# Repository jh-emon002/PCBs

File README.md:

## Images of the PCBs

### 1. AC to DC converter
A simple full bridge diode rectifier with smoothing capacitor and an indicator LED. It takes AC input in one side and outputs DC in the another.

### 2. Transformerless Power Supply
A 70x40 mm PCB that takes 110-220V AC at one side and outputs a stable 5V DC at another terminal. As there is no transformer, the circuit is compact and cheap.

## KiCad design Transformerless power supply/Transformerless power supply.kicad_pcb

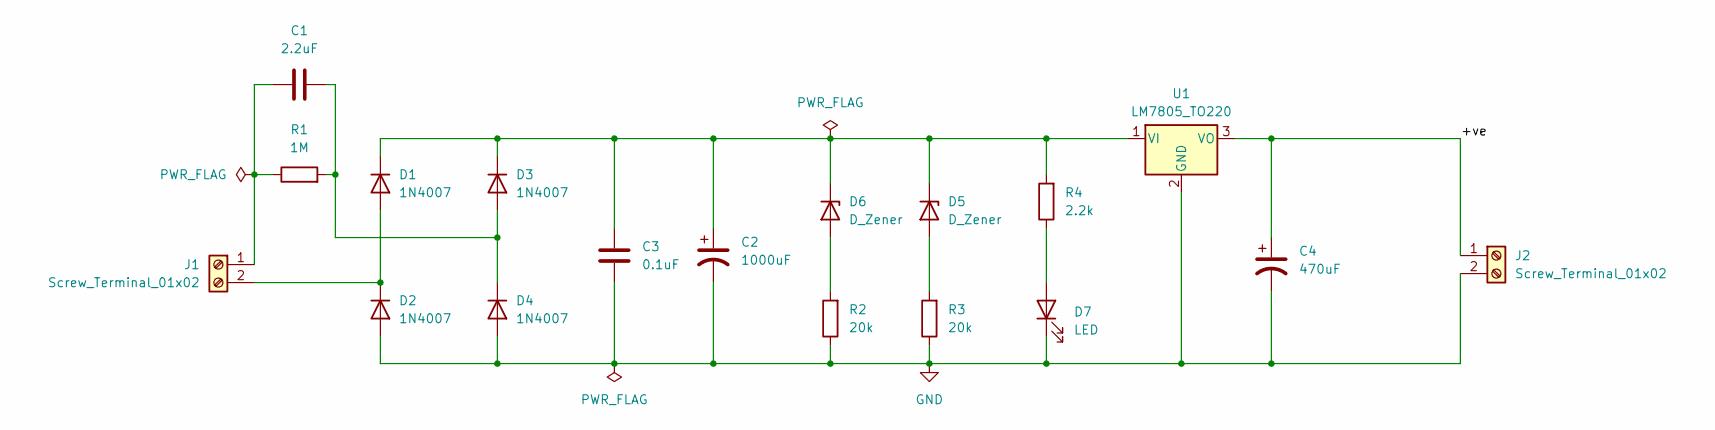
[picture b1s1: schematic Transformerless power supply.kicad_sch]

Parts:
C1: 2.2uF; C_Rect_L18.0mm_W5.0mm_P15.00mm_FKS3_FKP3
C2: 1000uF; CP_Radial_D10.0mm_P2.50mm
C3: 0.1uF; C_Disc_D4.7mm_W2.5mm_P5.00mm
C4: 470uF; CP_Radial_D10.0mm_P2.50mm
D1, D2, D3, D4: 1N4007; D_DO-41_SOD81_P10.16mm_Horizontal
D5, D6: D_Zener; D_DO-201_P15.24mm_Horizontal
D7: LED; LED_D5.0mm
J1, J2: Screw_Terminal_01x02; TerminalBlock_MaiXu_MX126-5.0-02P_1x02_P5.00mm
R1: 1M; R_Axial_DIN0204_L3.6mm_D1.6mm_P5.08mm_Horizontal
R2, R3: 20k; R_Axial_DIN0204_L3.6mm_D1.6mm_P5.08mm_Horizontal
R4: 2.2k; R_Axial_DIN0204_L3.6mm_D1.6mm_P5.08mm_Horizontal
U1: LM7805_TO220; TO-220-3_Vertical

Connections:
/+ve: C4.1, J2.1, U1.3 (VO)
GND: C2.2, C3.2, C4.2, D2.2 (A), D4.2 (A), D7.1 (K), J2.2, R2.1, R3.1, U1.2 (GND)
unnamed: D1.2 (A), D2.1 (K), J1.2
unnamed: C2.1, C3.1, D1.1 (K), D3.1 (K), D5.1 (K), D6.1 (K), R4.2, U1.1 (VI)
unnamed: C1.2, D3.2 (A), D4.1 (K), R1.2
unnamed: D5.2 (A), R3.2
unnamed: D6.2 (A), R2.2
unnamed: D7.2 (A), R4.1
unnamed: C1.1, J1.1, R1.1

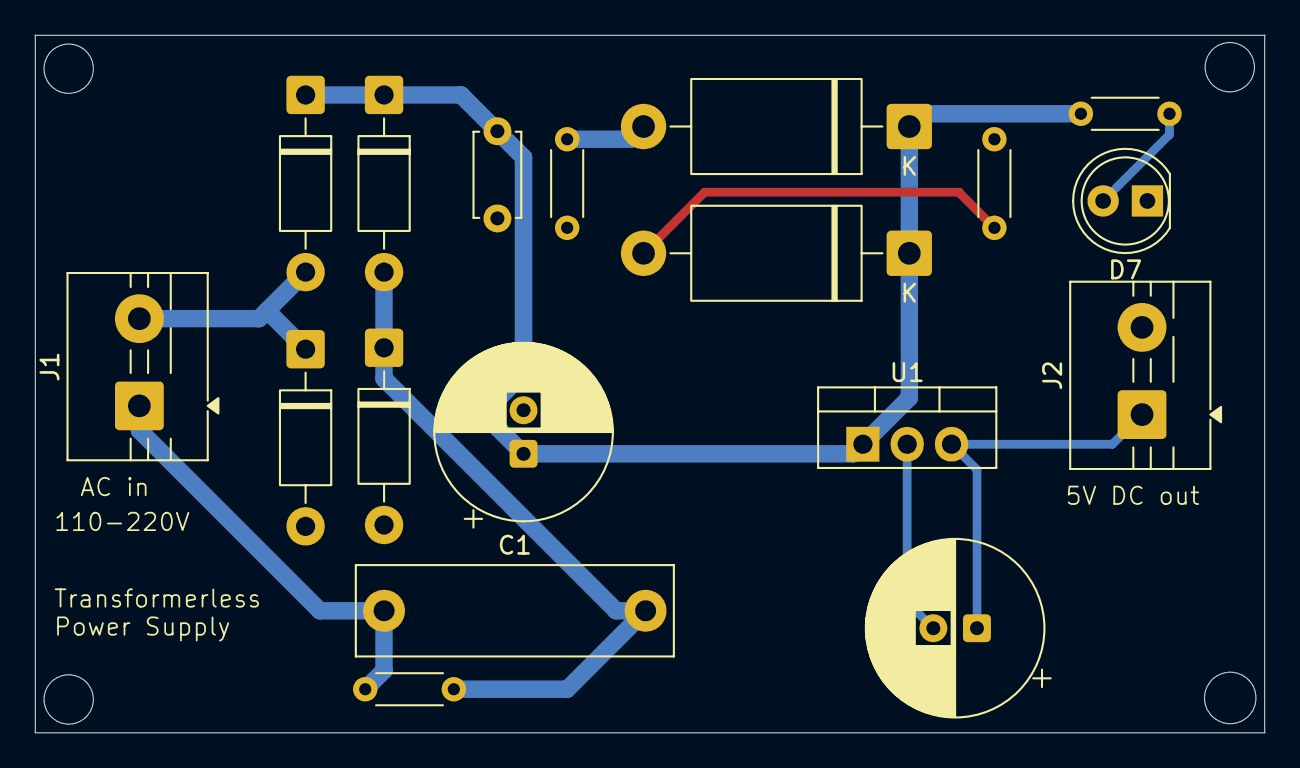
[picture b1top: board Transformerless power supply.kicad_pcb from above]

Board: 2 copper layers, 70.5 x 40.0 mm, 18 parts (0 on the bottom side), 9 nets.

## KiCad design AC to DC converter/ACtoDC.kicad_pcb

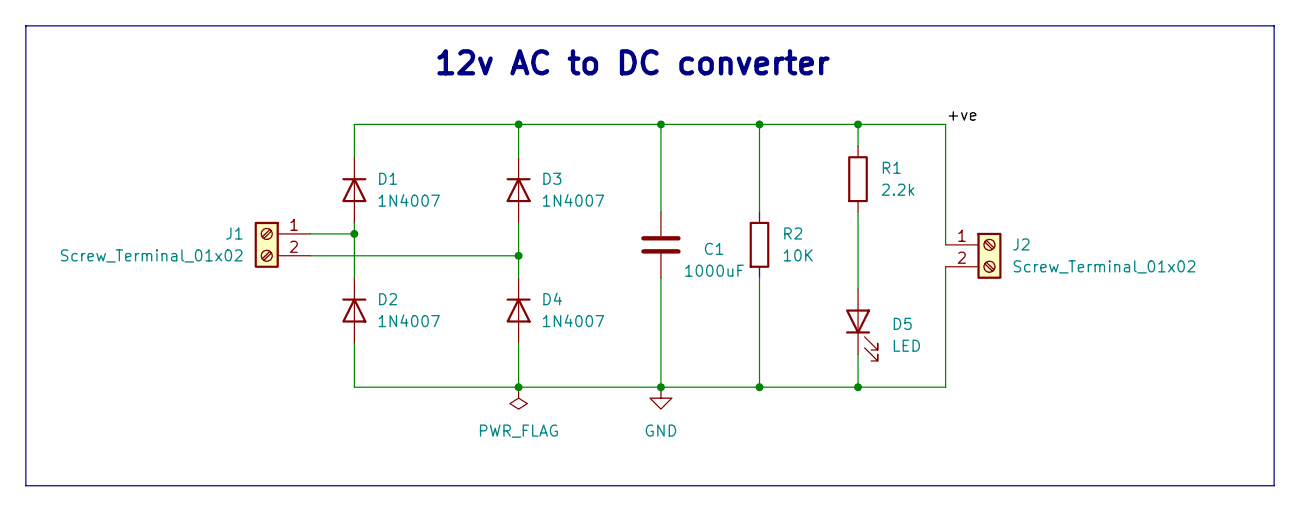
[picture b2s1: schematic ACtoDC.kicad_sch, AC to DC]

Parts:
C1: 1000uF; CP_Radial_D8.0mm_P3.80mm
D1, D2, D3, D4: 1N4007; D_DO-41_SOD81_P10.16mm_Horizontal
D5: LED; LED_D5.0mm
J1, J2: Screw_Terminal_01x02; TerminalBlock_MaiXu_MX126-5.0-02P_1x02_P5.00mm
R1: 2.2k; R_Axial_DIN0204_L3.6mm_D1.6mm_P7.62mm_Horizontal
R2: 10K; R_Axial_DIN0204_L3.6mm_D1.6mm_P7.62mm_Horizontal

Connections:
/+ve: C1.1, D1.1 (K), D3.1 (K), J2.1, R1.1, R2.1
GND: C1.2, D2.2 (A), D4.2 (A), D5.1 (K), J2.2, R2.2
unnamed: D1.2 (A), D2.1 (K), J1.1
unnamed: D3.2 (A), D4.1 (K), J1.2
unnamed: D5.2 (A), R1.2

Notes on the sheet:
12v AC to DC converter

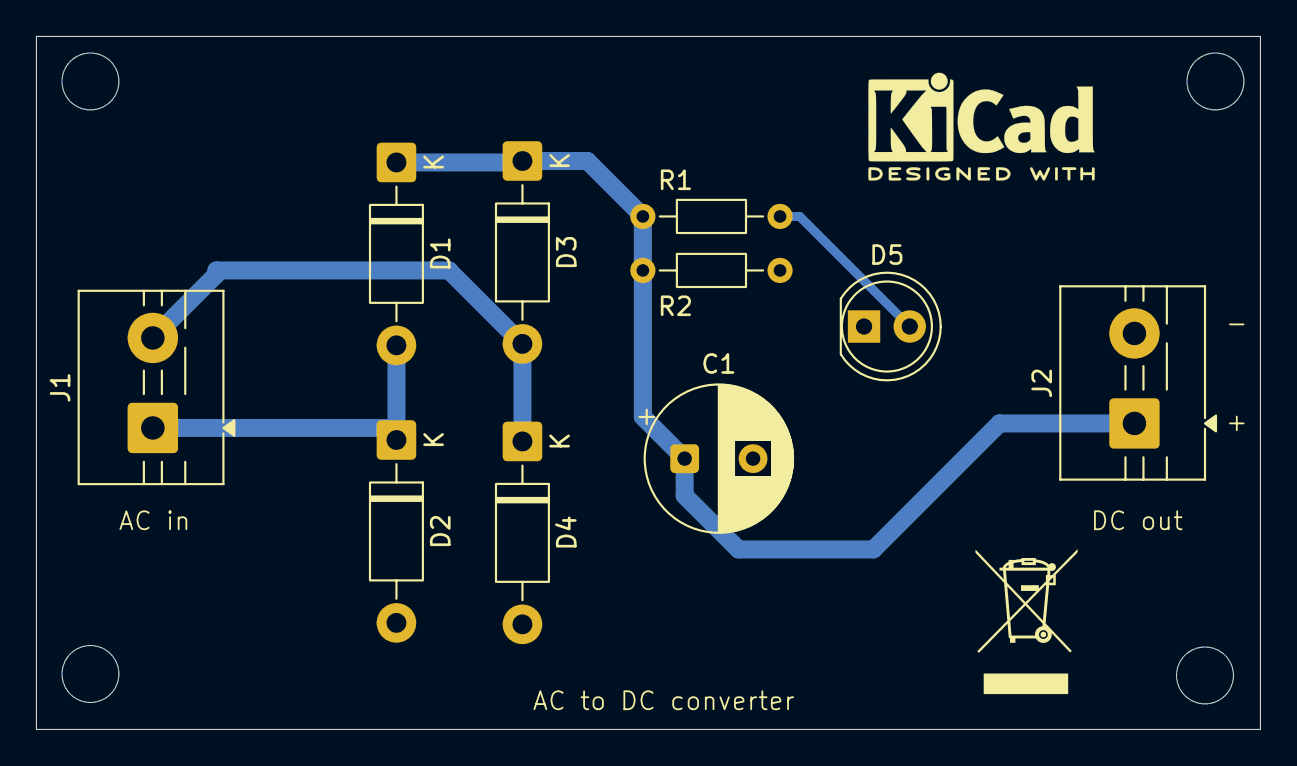
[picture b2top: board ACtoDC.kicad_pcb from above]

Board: 2 copper layers, 68.0 x 38.5 mm, 10 parts (0 on the bottom side), 5 nets.

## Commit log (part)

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2026-06-27 Create image
2026-06-27 Create x
2026-06-27 Add images section for AC to DC converter
2026-06-27 Add description for AC to DC converter in README
    Added a description for the AC to DC converter image.
